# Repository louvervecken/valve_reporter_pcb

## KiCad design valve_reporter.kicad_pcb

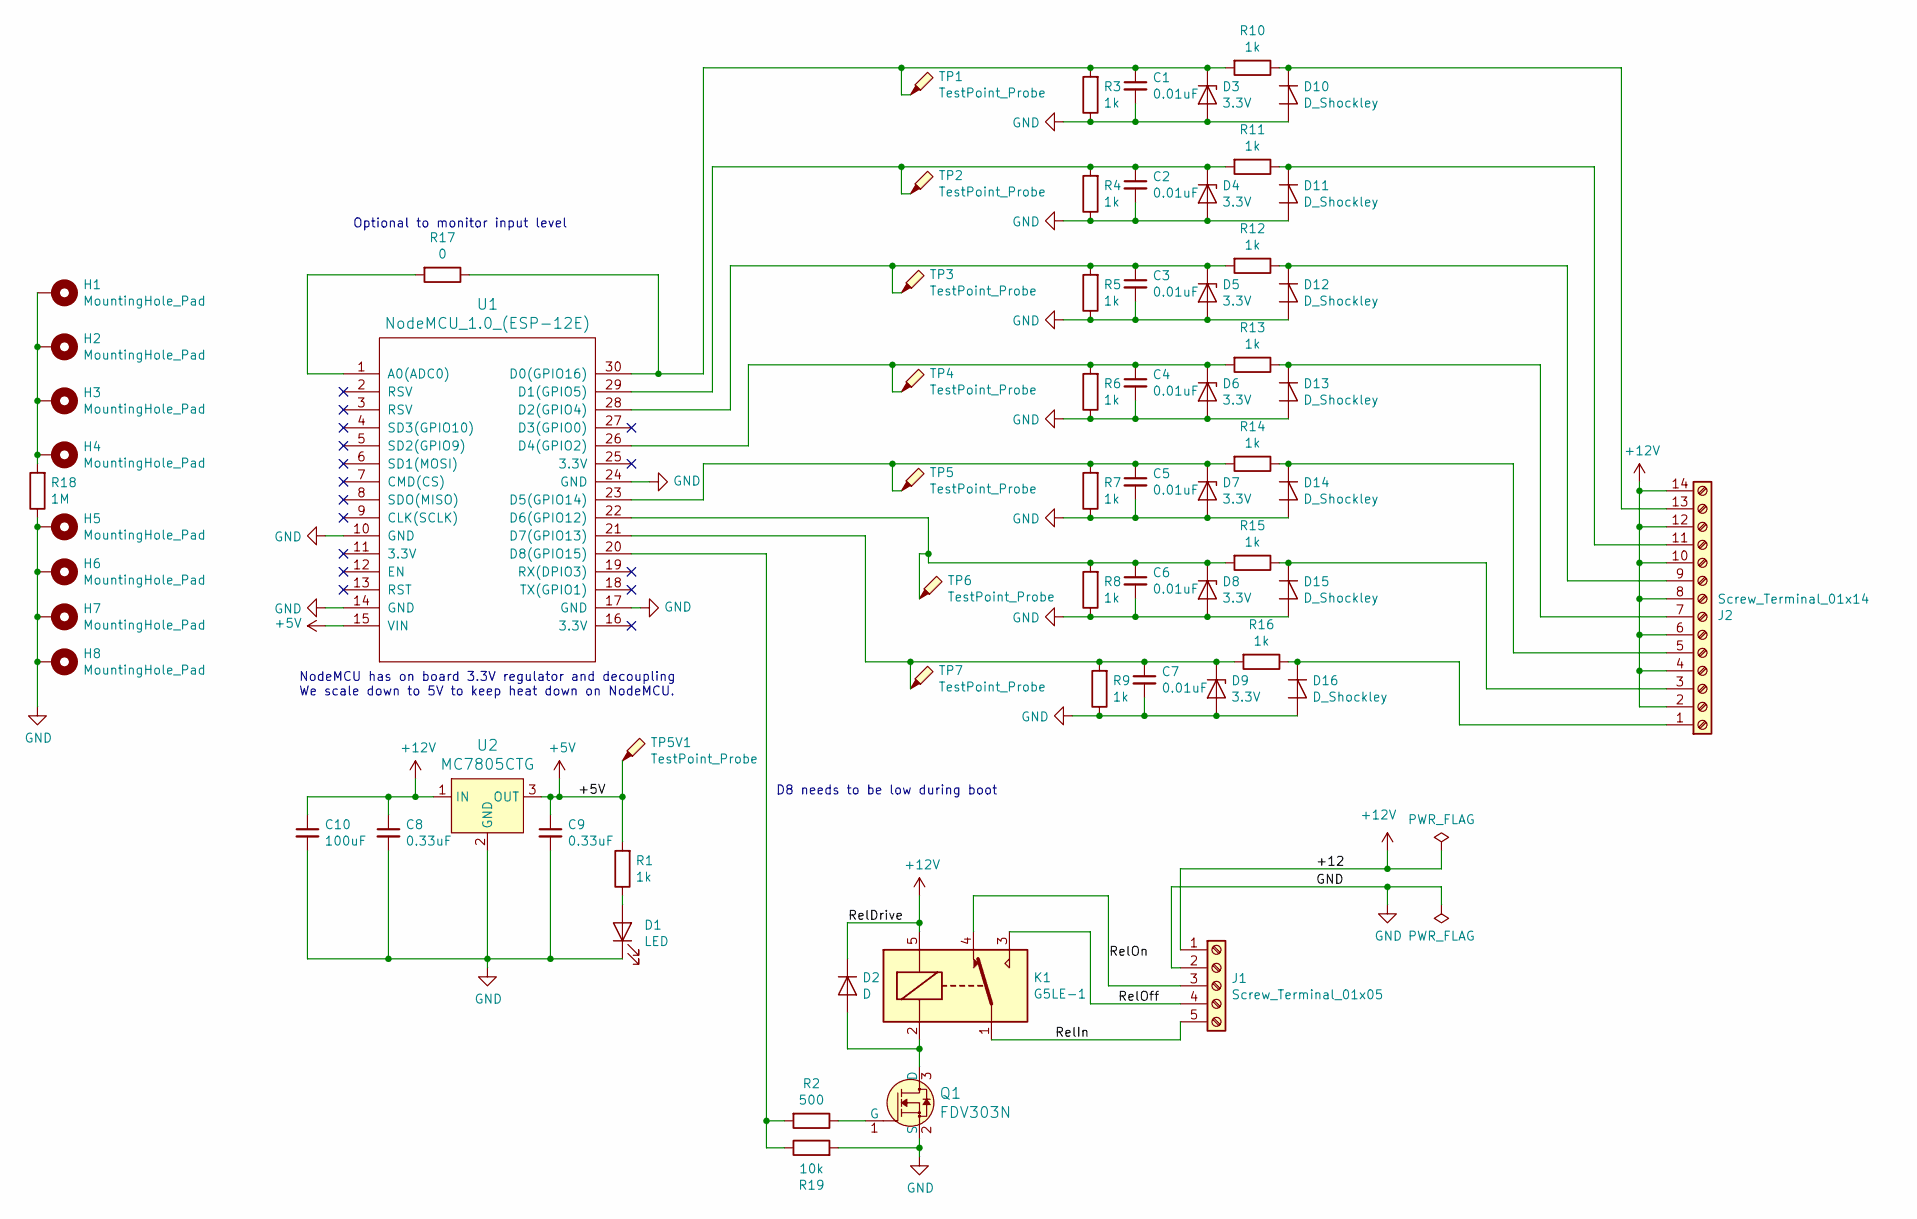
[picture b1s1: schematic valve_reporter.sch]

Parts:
C1, C2, C3, C4, C5, C6, C7: 0.01uF; C_1206_3216Metric_Pad1.42x1.75mm_HandSolder
C8, C9: 0.33uF; C_1206_3216Metric_Pad1.42x1.75mm_HandSolder
C10: 100uF; C_2816_7142Metric_Pad3.20x4.45mm_HandSolder
D1: LED; LED_1206_3216Metric_Pad1.42x1.75mm_HandSolder
D2: D; D_1206_3216Metric_Pad1.42x1.75mm_HandSolder
D3, D4, D5, D6, D7, D8, D9: 3.3V; D_SOD-323_HandSoldering
D10, D11, D12, D13, D14, D15, D16: D_Shockley; D_SOD-323_HandSoldering
H1, H2, H3, H4, H5, H6, H7, H8: MountingHole_Pad; MountingHole_3.2mm_M3_ISO7380_Pad
J1: Screw_Terminal_01x05; TerminalBlock_Phoenix_PT-1,5-5-5.0-H_1x05_P5.00mm_Horizonta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
J2: Screw_Terminal_01x14; TerminalBlock_Phoenix_PT-1,5-14-3.5-H_1x14_P3.50mm_Horizont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
K1: G5LE-1; Relay_SPDT_Omron-G5LE-1
Q1: FDV303N; TSOT-23_HandSoldering; MPN FDV303N; Digi-Key_PN FDV303NCT-ND
R1, R3, R4, R5, R6, R7, R8, R9, R10, R11, R12, R13, R14, R15, R16: 1k; R_1206_3216Metric_Pad1.42x1.75mm_HandSolder
R2: 500; R_1206_3216Metric_Pad1.42x1.75mm_HandSolder
R17: 0; R_1206_3216Metric_Pad1.42x1.75mm_HandSolder
R18: 1M; R_1206_3216Metric_Pad1.42x1.75mm_HandSolder
R19: 10k; R_1206_3216Metric_Pad1.42x1.75mm_HandSolder
TP1, TP2, TP3, TP4, TP5, TP5V1, TP6, TP7: TestPoint_Probe; TestPoint_THTPad_D2.0mm_Drill1.0mm
U1: NodeMCU_1.0_(ESP-12E); NodeMCU-LoLinV3
U2: MC7805CTG; TO-220-3; MPN MC7805CTG; Digi-Key_PN MC7805CTGOS-ND

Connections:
+5V: C9.1, R1.2, TP5V1.1, U1.15 (VIN), U2.3 (OUT)
+12V: C8.1, C10.1, D2.1 (K), J1.1, J2.2, J2.4, J2.6, J2.8, J2.10, J2.12, J2.14, K1.5, U2.1 (IN)
/RelIn: J1.5, K1.1
/RelOff: J1.4, K1.3
/RelOn: J1.3, K1.4
GND: C1.2, C2.2, C3.2, C4.2, C5.2, C6.2, C7.2, C8.2, C9.2, C10.2, D1.1 (K), D3.2 (A), D4.2 (A), D5.2 (A), D6.2 (A), D7.2 (A), D8.2 (A), D9.2 (A), D10.2 (A), D11.2 (A), D12.2 (A), D13.2 (A), D14.2 (A), D15.2 (A), D16.2 (A), H5.1, H6.1, H7.1, H8.1, J1.2, Q1.2 (S), R3.1, R4.1, R5.1, R6.1, R7.1, R8.1, R9.1, R18.1, R19.2, U1.10 (GND), U1.14 (GND), U1.17 (GND), U1.24 (GND), U2.2 (GND)
unnamed: C1.1, D3.1 (K), R3.2, R10.2, R17.1, TP1.1, U1.30 (D0(GPIO16))
unnamed: C2.1, D4.1 (K), R4.2, R11.2, TP2.1, U1.29 (D1(GPIO5))
unnamed: C3.1, D5.1 (K), R5.2, R12.2, TP3.1, U1.28 (D2(GPIO4))
unnamed: C4.1, D6.1 (K), R6.2, R13.2, TP4.1, U1.26 (D4(GPIO2))
unnamed: C5.1, D7.1 (K), R7.2, R14.2, TP5.1, U1.23 (D5(GPIO14))
unnamed: C6.1, D8.1 (K), R8.2, R15.2, TP6.1, U1.22 (D6(GPIO12))
unnamed: C7.1, D9.1 (K), R9.2, R16.2, TP7.1, U1.21 (D7(GPIO13))
unnamed: D1.2 (A), R1.1
unnamed: D2.2 (A), K1.2, Q1.3 (D)
unnamed: D10.1 (K), J2.13, R10.1
unnamed: D11.1 (K), J2.11, R11.1
unnamed: D12.1 (K), J2.9, R12.1
unnamed: D13.1 (K), J2.7, R13.1
unnamed: D14.1 (K), J2.5, R14.1
unnamed: D15.1 (K), J2.3, R15.1
unnamed: D16.1 (K), J2.1, R16.1
unnamed: H1.1, H2.1, H3.1, H4.1, R18.2
unnamed: Q1.1 (G), R2.1
unnamed: R17.2, U1.1 (A0(ADC0))
unnamed: R2.2, R19.1, U1.20 (D8(GPIO15))

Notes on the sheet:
D8 needs to be low during boot
Optional to monitor input level
NodeMCU has on board 3.3V regulator and decoupling We scale down to 5V to keep heat down on NodeMCU.

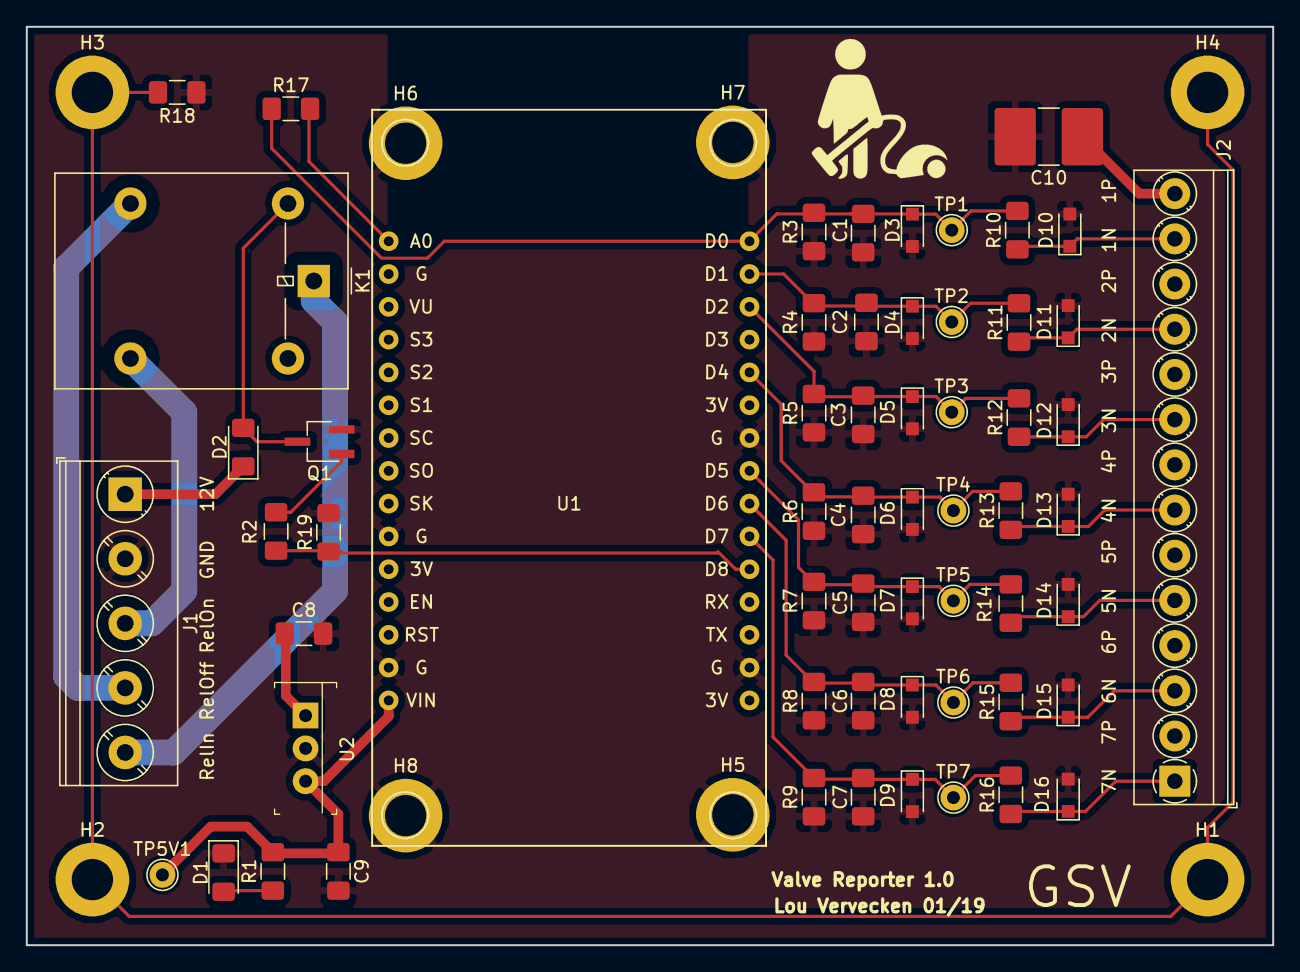
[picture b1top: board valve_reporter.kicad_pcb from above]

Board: 2 copper layers, 96.5 x 71.1 mm, 67 parts (0 on the bottom side), 26 nets.

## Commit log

2019-01-29 bom files
2019-01-29 Created layout
2019-01-30 Schematic is shaping up
2019-01-30 Add outputs
2019-01-31 Fixed non connect and increased keepout
2019-01-31 Extra decoupling
2019-01-31 Remove zip which was added by accident
2019-01-31 Move to handsolder pads to make live easier
2019-01-31 Add artwork again
2019-02-01 Use mosfet to drive relay add test points
    todo:
    - connect test points
    - SMD relay?...
    - check holes sizes
    - 12V power plane
2019-02-03 Test points, 12V plane, fancy BOM
